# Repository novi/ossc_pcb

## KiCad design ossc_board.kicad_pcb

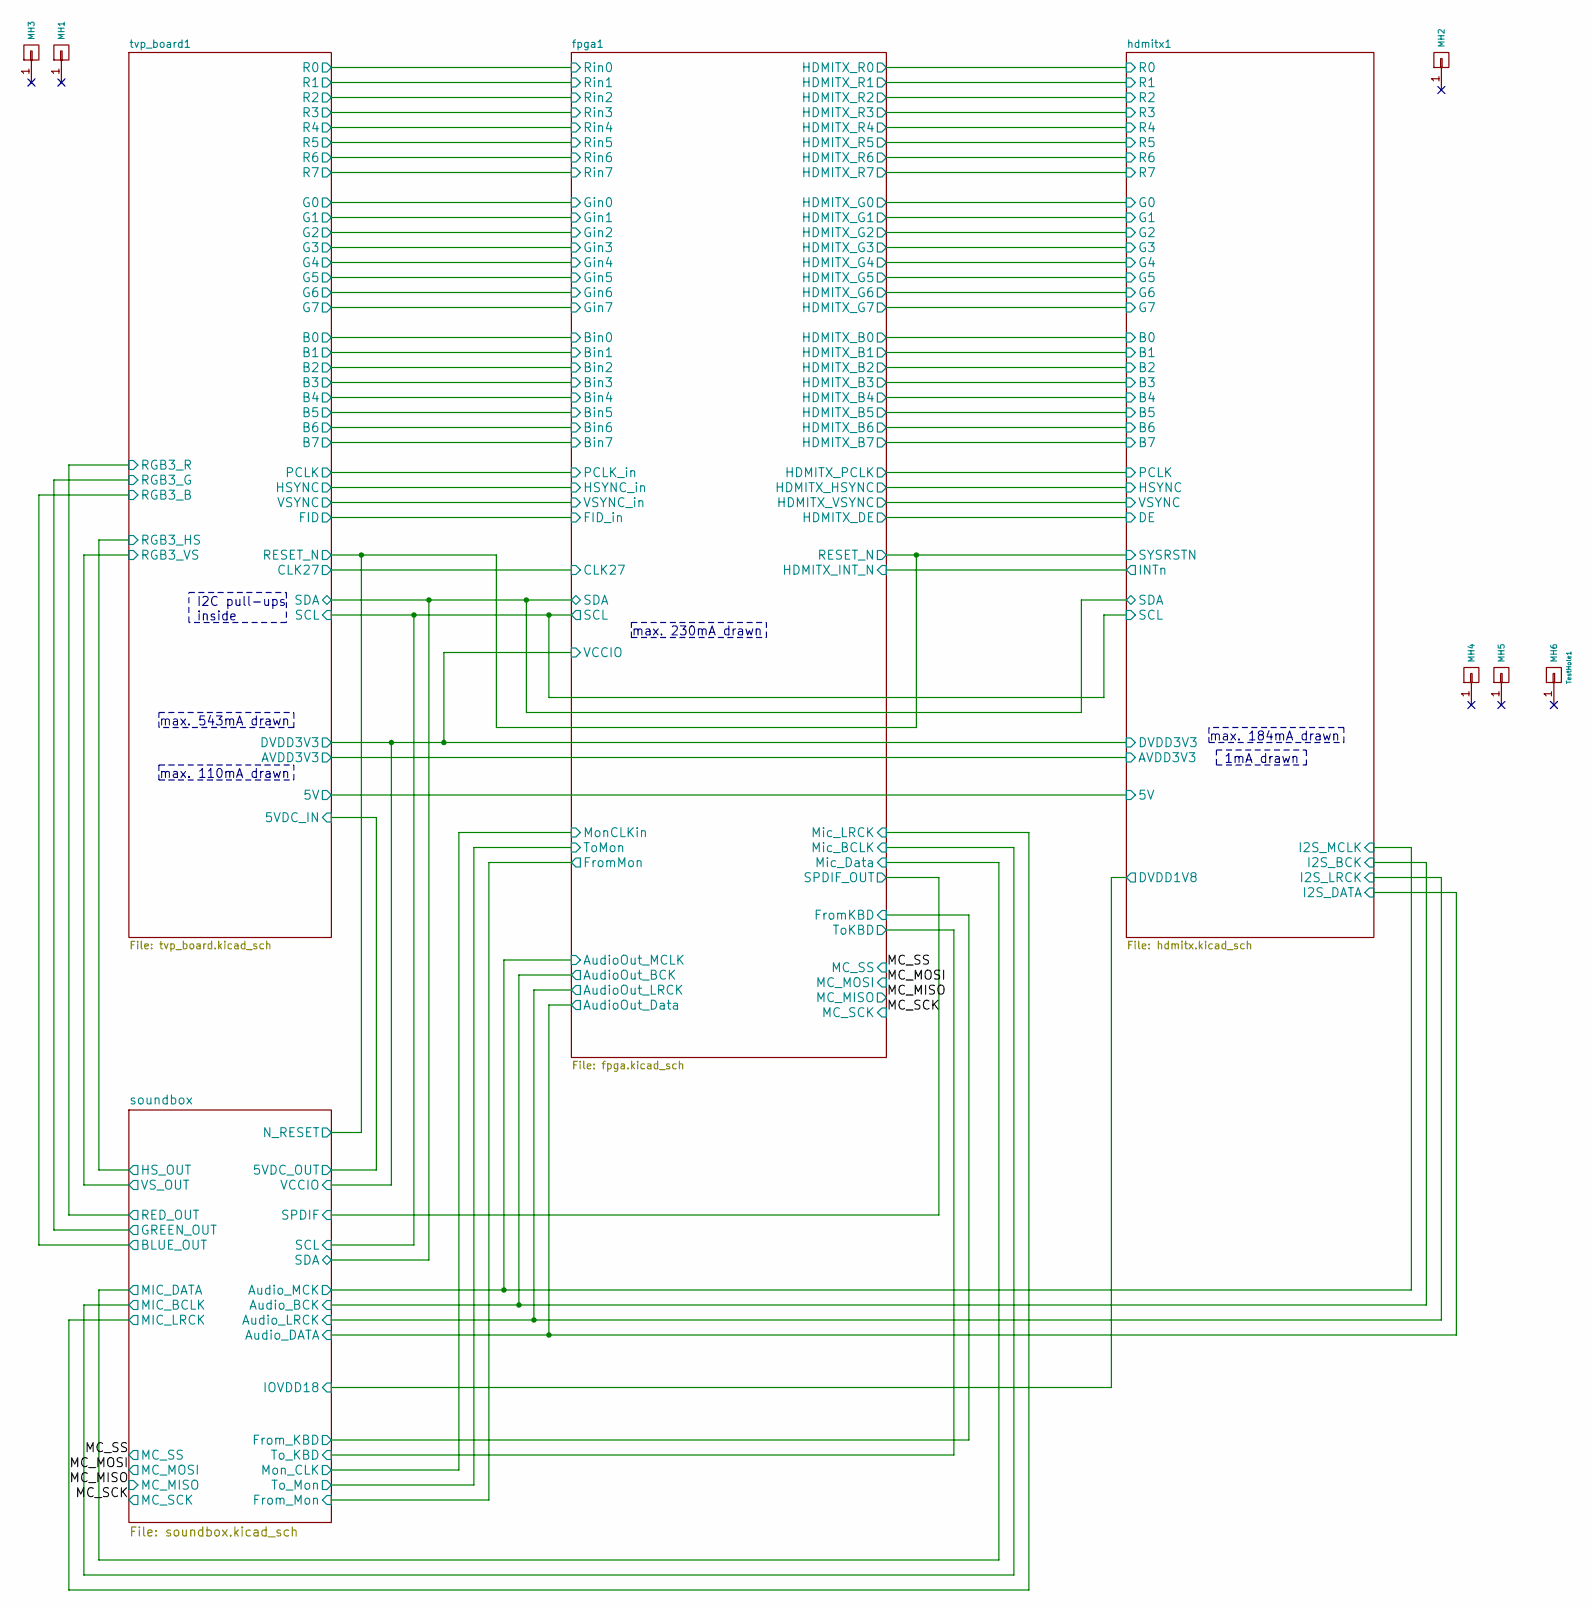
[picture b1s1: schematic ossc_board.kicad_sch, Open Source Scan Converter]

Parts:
MH1, MH2, MH3, MH4, MH5: CONN_1; MountingHole_2.7mm_M2.5
MH6: TestHole1; TestHole_1.0mm

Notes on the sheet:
1mA drawn
I2C pull-ups inside
max. 110mA drawn
max. 543mA drawn
max. 184mA drawn
max. 230mA drawn

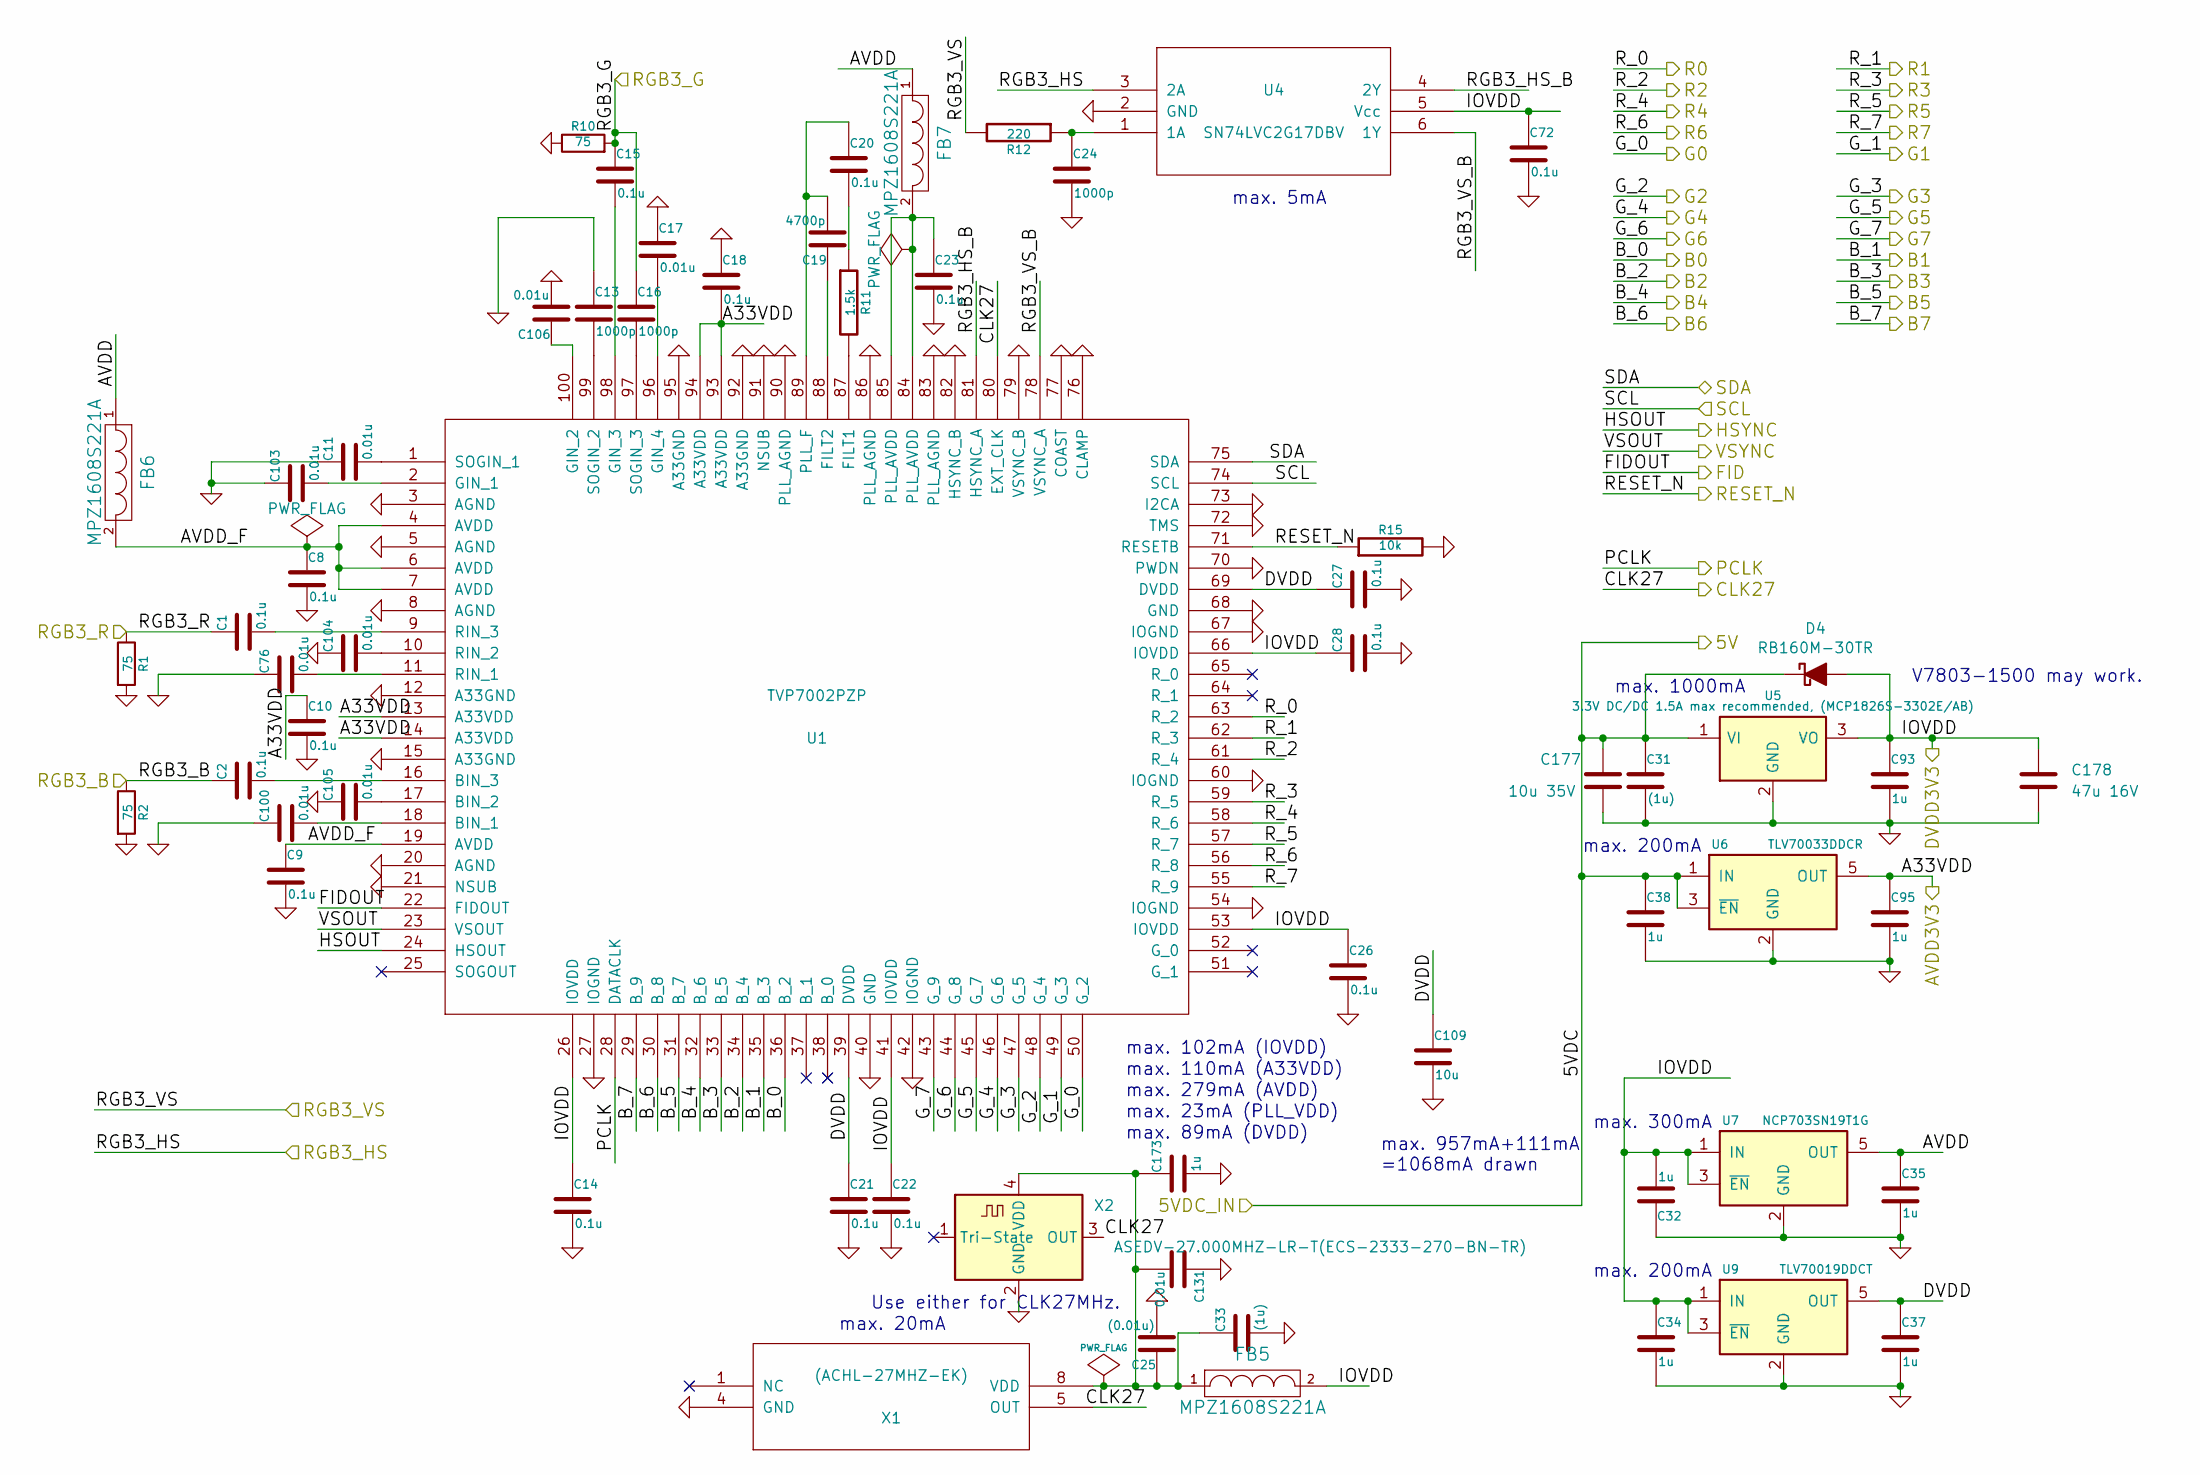
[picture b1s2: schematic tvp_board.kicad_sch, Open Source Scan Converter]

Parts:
C1, C2, C8, C9, C10, C14, C15, C18, C20, C21, C22, C23, C26, C27, C28, C72: 0.1u; C_0603_1608Metric_Pad1.05x0.95mm_HandSolder; Part ID GCJ188R71H104KA12D or GRM188R72A104MA35D
C11, C17, C76, C100, C103, C104, C105, C106, C131: 0.01u; C_0603_1608Metric_Pad1.05x0.95mm_HandSolder; Part ID GCM188R72A103KA37J
C13, C16, C24: 1000p; C_0603_1608Metric_Pad1.05x0.95mm_HandSolder
C19: 4700p; C_0603_1608Metric_Pad1.05x0.95mm_HandSolder
C25: (0.01u); C_0603_1608Metric_Pad1.05x0.95mm_HandSolder; Part ID GCM188R72A103KA37J
C31, C33: (1u); C_0603_1608Metric_Pad1.08x0.95mm_HandSolder; Part ID GRT188R61H105KE13D
C32, C34, C35, C37, C38, C93, C95, C173: 1u; C_0603_1608Metric_Pad1.05x0.95mm_HandSolder; Part ID GRT188R61H105KE13D
C109: 10u; C_0603_1608Metric_Pad1.05x0.95mm_HandSolder; Part ID ZRB18AR61E106ME01L
C177: 10u 35V; C_1210_3225Metric_Pad1.33x2.70mm_HandSolder; Part ID GRM32ER7YA106KA12
C178: 47u 16V; C_1210_3225Metric_Pad1.33x2.70mm_HandSolder; Part ID GRM32EC81C476KE15L
D4: RB160M-30TR; D_SOD-123_HandSoldering
FB5, FB6, FB7: MPZ1608S221A; L_0603_1608Metric_Pad1.05x0.95mm_HandSolder
R1, R2, R10: 75; R_0603_1608Metric_Pad1.05x0.95mm_HandSolder
R11: 1.5k; R_0603_1608Metric_Pad1.05x0.95mm_HandSolder
R12: 220; R_0603_1608Metric_Pad1.05x0.95mm_HandSolder
R15: 10k; R_0603_1608Metric_Pad1.05x0.95mm_HandSolder
U1: TVP7002PZP; TQFP-100_thermal
U4: SN74LVC2G17DBV; SOT-23-6_Handsoldering
U5: 3.3V DC/DC 1.5A max recommended, (MCP1826S-3302E/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; TO-220-3_Vertical; Part ID MCP1826S-3302E/AB
U6: TLV70033DDCR; SOT-23-5_HandSoldering
U7: NCP703SN19T1G; SOT-23-5_Handsoldering
U9: TLV70019DDCT; SOT-23-5_Handsoldering
X1: (ACHL-27MHZ-EK); ACHL-OSC
X2: ASEDV-27.000MHZ-LR-T(ECS-2333-270-BN-TR); Oscillator_SMD_SeikoEpson_SG8002CE-4Pin_3.2x2.5mm_HandSolde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

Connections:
/fpga1/RESET_N: R15.1, U1.71 (RESETB); also elsewhere on the board
/fpga1/SCL: U1.74 (SCL); also elsewhere on the board
/fpga1/SDA: U1.75 (SDA); also elsewhere on the board
/hdmitx1/5V: C31.1, C38.1, C177.1, D4.1 (K), U5.1 (VI), U6.1 (IN), U6.3 (~EN); also elsewhere on the board
/hdmitx1/AVCC3V3: C10.1, C18.2, C95.1, U1.13 (A33VDD), U1.14 (A33VDD), U1.93 (A33VDD), U1.94 (A33VDD), U6.5 (OUT); also elsewhere on the board
/tvp_board1/AVDD: C35.1, FB6.1, FB7.1, U7.5 (OUT)
/tvp_board1/AVDD_F: C8.1, C9.1, FB6.2, U1.4 (AVDD), U1.6 (AVDD), U1.7 (AVDD), U1.19 (AVDD)
/tvp_board1/B_0: U1.36 (B_2); also elsewhere on the board
/tvp_board1/B_1: U1.35 (B_3); also elsewhere on the board
/tvp_board1/B_2: U1.34 (B_4); also elsewhere on the board
/tvp_board1/B_3: U1.33 (B_5); also elsewhere on the board
/tvp_board1/B_4: U1.32 (B_6); also elsewhere on the board
/tvp_board1/B_5: U1.31 (B_7); also elsewhere on the board
/tvp_board1/B_6: U1.30 (B_8); also elsewhere on the board
/tvp_board1/B_7: U1.29 (B_9); also elsewhere on the board
/tvp_board1/CLK27: U1.80 (EXT_CLK), X1.5 (OUT), X2.3 (OUT); also elsewhere on the board
/tvp_board1/DVDD: C21.1, C27.1, C37.1, C109.1, U1.39 (DVDD), U1.69 (DVDD), U9.5 (OUT)
/tvp_board1/FIDOUT: U1.22 (FIDOUT); also elsewhere on the board
/tvp_board1/G_0: U1.50 (G_2); also elsewhere on the board
/tvp_board1/G_1: U1.49 (G_3); also elsewhere on the board
/tvp_board1/G_2: U1.48 (G_4); also elsewhere on the board
/tvp_board1/G_3: U1.47 (G_5); also elsewhere on the board
/tvp_board1/G_4: U1.46 (G_6); also elsewhere on the board
/tvp_board1/G_5: U1.45 (G_7); also elsewhere on the board
/tvp_board1/G_6: U1.44 (G_8); also elsewhere on the board
/tvp_board1/G_7: U1.43 (G_9); also elsewhere on the board
/tvp_board1/HSOUT: U1.24 (HSOUT); also elsewhere on the board
/tvp_board1/PCLK: U1.28 (DATACLK); also elsewhere on the board
/tvp_board1/RGB3_B: C2.1, R2.1; also elsewhere on the board
/tvp_board1/RGB3_G: C15.1, C16.1, R10.2; also elsewhere on the board
/tvp_board1/RGB3_HS: U4.3 (2A); also elsewhere on the board
/tvp_board1/RGB3_HS_B: U1.81 (HSYNC_A), U4.4 (2Y)
/tvp_board1/RGB3_R: C1.1, R1.1; also elsewhere on the board
/tvp_board1/RGB3_VS: R12.2; also elsewhere on the board
/tvp_board1/RGB3_VS_B: U1.78 (VSYNC_A), U4.6 (1Y)
/tvp_board1/R_0: U1.63 (R_2); also elsewhere on the board
/tvp_board1/R_1: U1.62 (R_3); also elsewhere on the board
/tvp_board1/R_2: U1.61 (R_4); also elsewhere on the board
/tvp_board1/R_3: U1.59 (R_5); also elsewhere on the board
/tvp_board1/R_4: U1.58 (R_6); also elsewhere on the board
/tvp_board1/R_5: U1.57 (R_7); also elsewhere on the board
/tvp_board1/R_6: U1.56 (R_8); also elsewhere on the board
/tvp_board1/R_7: U1.55 (R_9); also elsewhere on the board
/tvp_board1/VSOUT: U1.23 (VSOUT); also elsewhere on the board
GND: C8.2, C9.2, C10.2, C11.1, C13.1, C14.2, C17.1, C18.1, C21.2, C22.2, C23.2, C24.2, C25.2, C26.2, C27.2, C28.2, C31.2, C32.1, C33.2, C34.2, C35.2, C37.2, C38.2, C72.2, C76.1, C93.2, C95.2, C100.1, C103.1, C104.1, C105.1, C106.2, C109.2, C131.1, C173.2, C177.2, C178.2, R1.2, R2.2, R10.1, R15.2, U1.3 (AGND), U1.5 (AGND), U1.8 (AGND), U1.12 (A33GND), U1.15 (A33GND), U1.20 (AGND), U1.21 (NSUB), U1.27 (IOGND), U1.40 (GND), U1.42 (IOGND), U1.54 (IOGND), U1.60 (IOGND), U1.67 (IOGND), U1.68 (GND), U1.70 (PWDN), U1.72 (TMS), U1.73 (I2CA), U1.76 (CLAMP), U1.77 (COAST), U1.79 (VSYNC_B), U1.82 (HSYNC_B), U1.83 (PLL_AGND), U1.86 (PLL_AGND), U1.90 (PLL_AGND), U1.91 (NSUB), U1.92 (A33GND), U1.95 (A33GND), U4.2 (GND), U5.2 (GND), U6.2 (GND), U7.2 (GND), U9.2 (GND), X1.4 (GND), X2.2 (GND); also elsewhere on the board
unnamed: C20.2, R11.1
unnamed: C23.1, FB7.2, U1.84 (PLL_AVDD), U1.85 (PLL_AVDD)
unnamed: C100.2, U1.18 (BIN_1)
unnamed: C105.2, U1.17 (BIN_2)
unnamed: C2.2, U1.16 (BIN_3)
unnamed: R11.2, U1.87 (FILT1)
unnamed: C19.1, U1.88 (FILT2)
unnamed: C103.2, U1.2 (GIN_1)
unnamed: C106.1, U1.100 (GIN_2)
unnamed: C15.2, U1.98 (GIN_3)
unnamed: C17.2, U1.96 (GIN_4)
unnamed: C19.2, C20.1, U1.89 (PLL_F)
unnamed: C76.2, U1.11 (RIN_1)
unnamed: C104.2, U1.10 (RIN_2)
unnamed: C1.2, U1.9 (RIN_3)
unnamed: C11.2, U1.1 (SOGIN_1)
unnamed: C13.2, U1.99 (SOGIN_2)
unnamed: C16.2, U1.97 (SOGIN_3)
unnamed: C24.1, R12.1, U4.1 (1A)
unnamed: C25.1, C33.1, C131.2, C173.1, FB5.1, X1.8 (VDD), X2.4 (VDD)
VCC: C14.1, C22.1, C26.1, C28.1, C32.2, C34.1, C72.1, C93.1, C178.1, D4.2 (A), FB5.2, U1.26 (IOVDD), U1.41 (IOVDD), U1.53 (IOVDD), U1.66 (IOVDD), U4.5 (Vcc), U5.3 (VO), U7.1 (IN), U7.3 (~EN), U9.1 (IN), U9.3 (~EN); also elsewhere on the board

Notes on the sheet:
max. 1000mA
max. 110mA (A33VDD)
max. 279mA (AVDD)
max. 300mA
max. 23mA (PLL_VDD)
V7803-1500 may work.
max. 200mA
max. 957mA+111mA =1068mA drawn
max. 102mA (IOVDD)
Use either for CLK27MHz.
max. 5mA
max. 20mA
max. 89mA (DVDD)

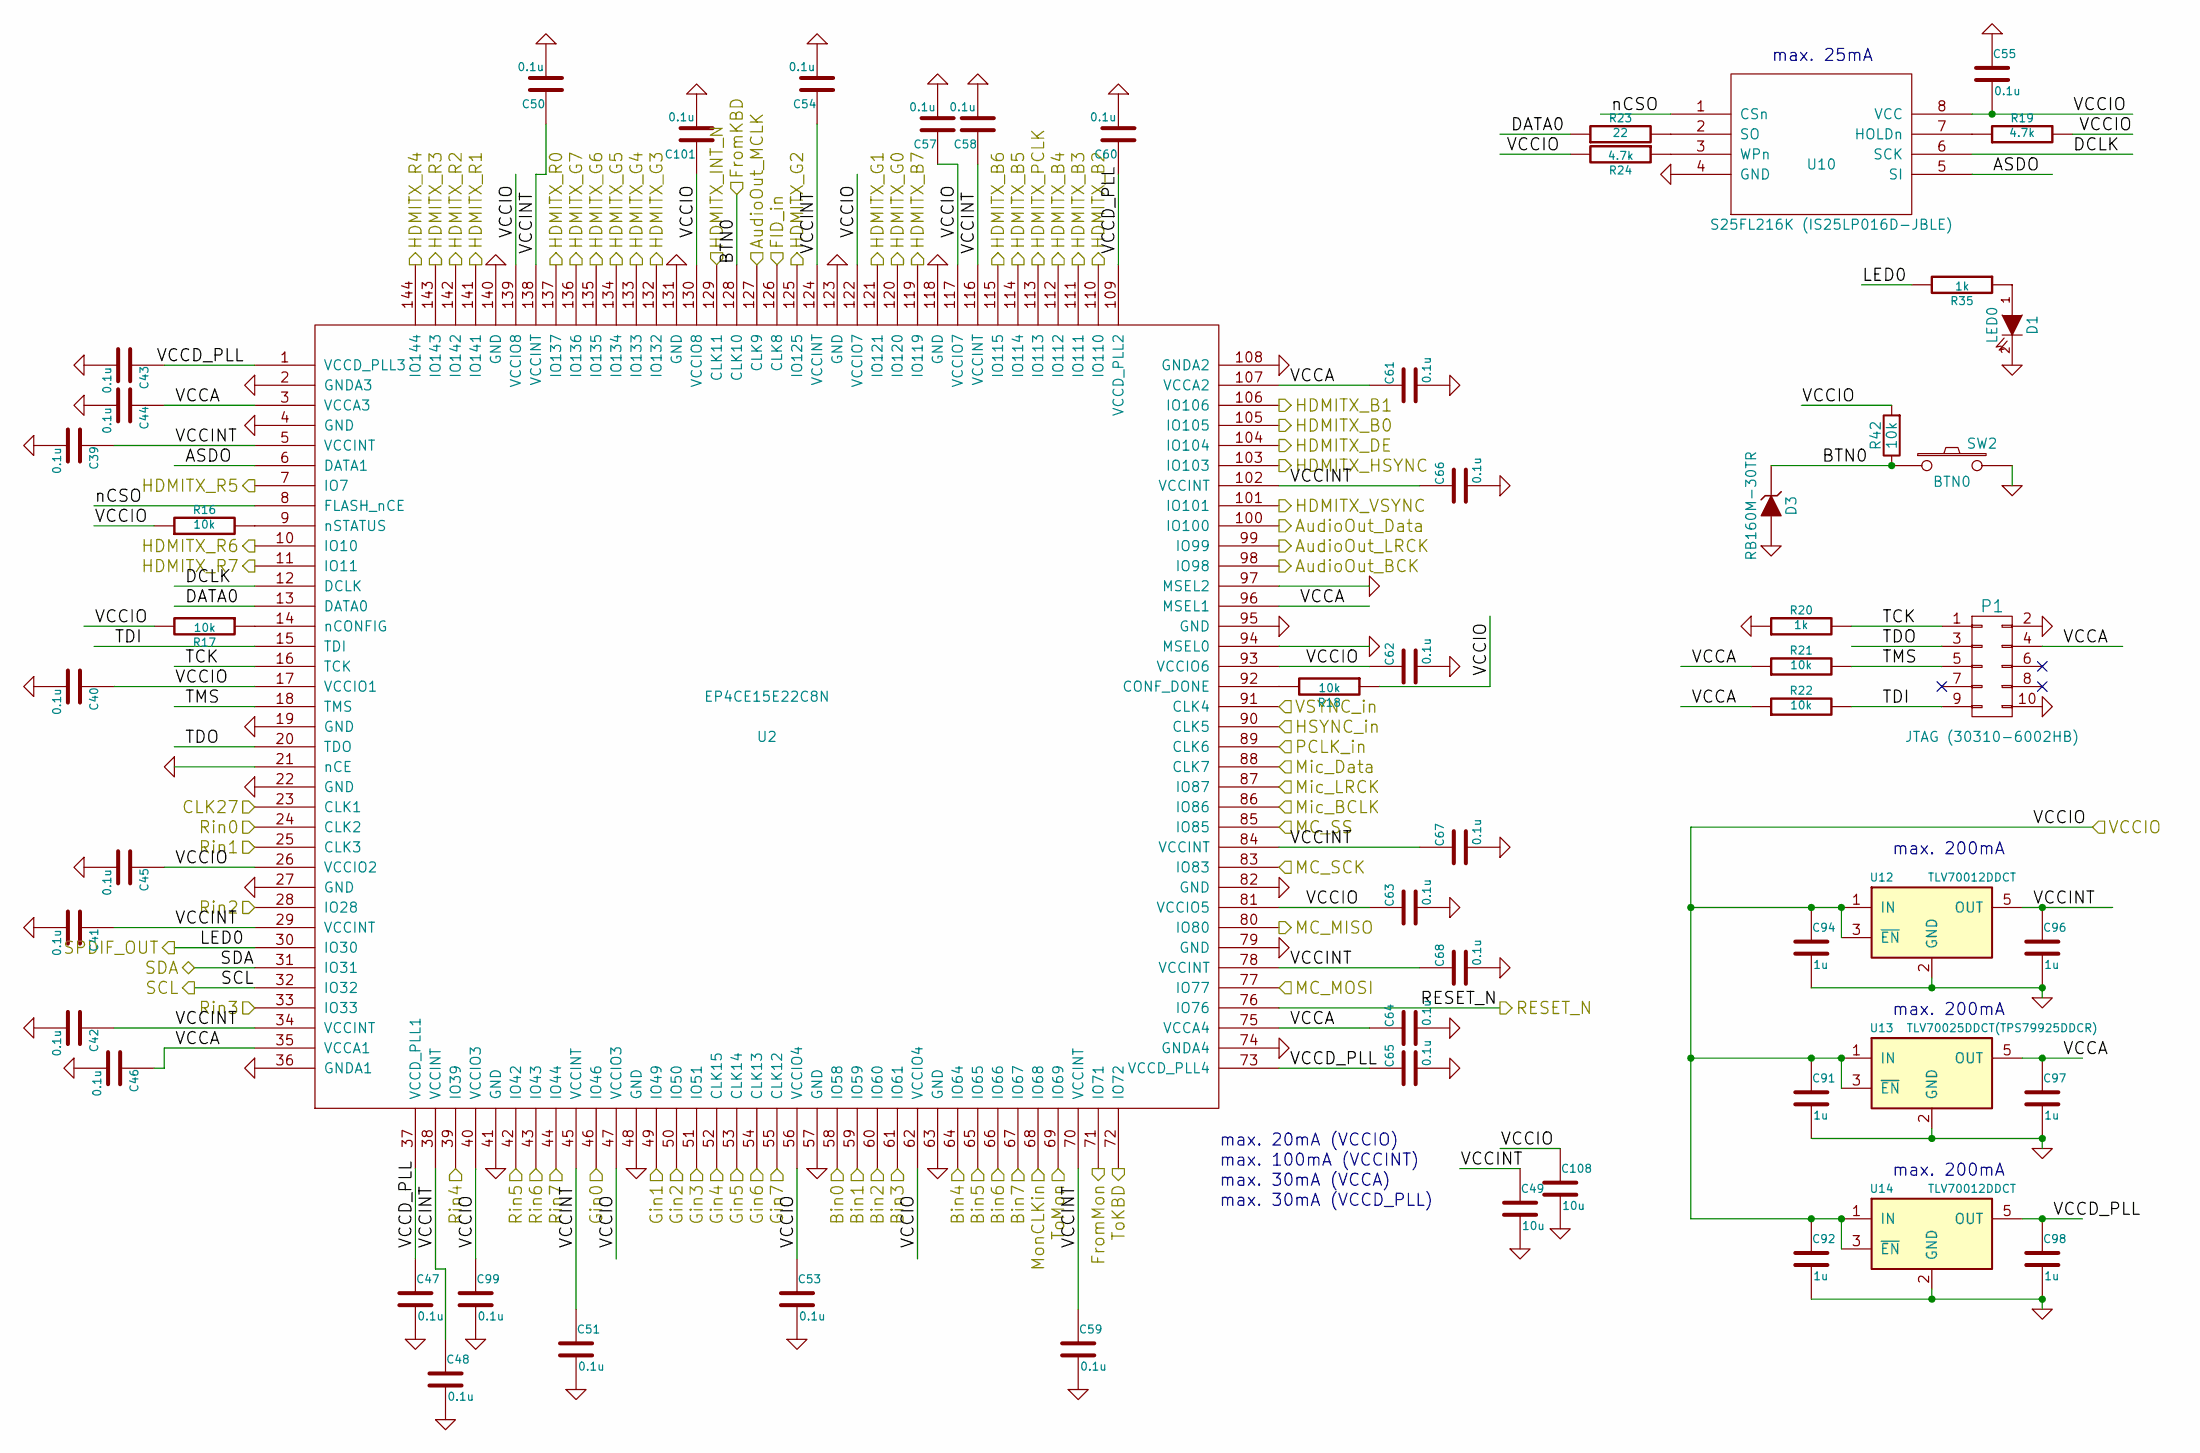
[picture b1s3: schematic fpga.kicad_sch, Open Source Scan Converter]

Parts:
C39, C40, C41, C42, C43, C44, C45, C46, C47, C48, C50, C51, C53, C54, C55, C57, C58, C59, C60, C61, C62, C63, C64, C65, C66, C67, C68, C99, C101: 0.1u; C_0603_1608Metric_Pad1.05x0.95mm_HandSolder; Part ID GCJ188R71H104KA12D or GRM188R72A104MA35D
C49, C108: 10u; C_0603_1608Metric_Pad1.05x0.95mm_HandSolder; Part ID ZRB18AR61E106ME01L
C91, C92, C94, C96, C97, C98: 1u; C_0603_1608Metric_Pad1.05x0.95mm_HandSolder; Part ID GRT188R61H105KE13D
D1: LED0; LED_D3.0mm_Horizontal_O1.27mm_Z6.0mm
D3: RB160M-30TR; D_SOD-123_HandSoldering
P1: JTAG (30310-6002HB); VASCH5x2
R16, R17, R18, R21, R22, R42: 10k; R_0603_1608Metric_Pad1.05x0.95mm_HandSolder
R19, R24: 4.7k; R_0603_1608Metric_Pad1.05x0.95mm_HandSolder
R20, R35: 1k; R_0603_1608Metric_Pad1.05x0.95mm_HandSolder
R23: 22; R_0603_1608Metric_Pad1.05x0.95mm_HandSolder
SW2: BTN0; SW_Tactile_SKHH_Angled; Part ID (1-1825027-1 / 2-1825027-0)
U2: EP4CE15E22C8N; TQFP-144_thermal
U10: S25FL216K (IS25LP016D-JBLE); SOIC-8_3.9x4.9mm_Pitch1.27mm_Handsoldering
U12, U14: TLV70012DDCT; SOT-23-5_Handsoldering
U13: TLV70025DDCT(TPS79925DDCR); SOT-23-5_Handsoldering

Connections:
/MC_MISO: U2.80 (IO80); also elsewhere on the board
/MC_MOSI: U2.77 (IO77); also elsewhere on the board
/MC_SCK: U2.83 (IO83); also elsewhere on the board
/MC_SS: U2.85 (IO85); also elsewhere on the board
/fpga1/ASDO: U2.6 (DATA1), U10.5 (SI)
/fpga1/BTN0: D3.1 (K), R42.1, SW2.1, U2.128 (CLK10); also elsewhere on the board
/fpga1/DATA0: R23.1, U2.13 (DATA0)
/fpga1/DCLK: U2.12 (DCLK), U10.6 (SCK)
/fpga1/FromMon: U2.71 (IO71); also elsewhere on the board
/fpga1/HDMITX_B0: U2.105 (IO105); also elsewhere on the board
/fpga1/HDMITX_B1: U2.106 (IO106); also elsewhere on the board
/fpga1/HDMITX_B2: U2.110 (IO110); also elsewhere on the board
/fpga1/HDMITX_B3: U2.111 (IO111); also elsewhere on the board
/fpga1/HDMITX_B4: U2.112 (IO112); also elsewhere on the board
/fpga1/HDMITX_B5: U2.114 (IO114); also elsewhere on the board
/fpga1/HDMITX_B6: U2.115 (IO115); also elsewhere on the board
/fpga1/HDMITX_B7: U2.119 (IO119); also elsewhere on the board
/fpga1/HDMITX_DE: U2.104 (IO104); also elsewhere on the board
/fpga1/HDMITX_G0: U2.120 (IO120); also elsewhere on the board
/fpga1/HDMITX_G1: U2.121 (IO121); also elsewhere on the board
/fpga1/HDMITX_G2: U2.125 (IO125); also elsewhere on the board
/fpga1/HDMITX_G3: U2.132 (IO132); also elsewhere on the board
/fpga1/HDMITX_G4: U2.133 (IO133); also elsewhere on the board
/fpga1/HDMITX_G5: U2.134 (IO134); also elsewhere on the board
/fpga1/HDMITX_G6: U2.135 (IO135); also elsewhere on the board
/fpga1/HDMITX_G7: U2.136 (IO136); also elsewhere on the board
/fpga1/HDMITX_HSYNC: U2.103 (IO103); also elsewhere on the board
/fpga1/HDMITX_INT_N: U2.129 (CLK11); also elsewhere on the board
/fpga1/HDMITX_PCLK: U2.113 (IO113); also elsewhere on the board
/fpga1/HDMITX_R0: U2.137 (IO137); also elsewhere on the board
/fpga1/HDMITX_R1: U2.141 (IO141); also elsewhere on the board
/fpga1/HDMITX_R2: U2.142 (IO142); also elsewhere on the board
/fpga1/HDMITX_R3: U2.143 (IO143); also elsewhere on the board
/fpga1/HDMITX_R4: U2.144 (IO144); also elsewhere on the board
/fpga1/HDMITX_R5: U2.7 (IO7); also elsewhere on the board
/fpga1/HDMITX_R6: U2.10 (IO10); also elsewhere on the board
/fpga1/HDMITX_R7: U2.11 (IO11); also elsewhere on the board
/fpga1/HDMITX_VSYNC: U2.101 (IO101); also elsewhere on the board
/fpga1/LED0: R35.2, U2.30 (IO30); also elsewhere on the board
/fpga1/Mic_BCLK: U2.86 (IO86); also elsewhere on the board
/fpga1/Mic_Data: U2.88 (CLK7); also elsewhere on the board
/fpga1/Mic_LRCK: U2.87 (IO87); also elsewhere on the board
/fpga1/MonCLKin: U2.68 (IO68); also elsewhere on the board
/fpga1/RESET_N: U2.76 (IO76); also elsewhere on the board
/fpga1/SCL: U2.32 (IO32); also elsewhere on the board
/fpga1/SDA: U2.31 (IO31); also elsewhere on the board
/fpga1/TCK: P1.1, R20.2, U2.16 (TCK)
/fpga1/TDI: P1.9, R22.2, U2.15 (TDI)
/fpga1/TDO: P1.3, U2.20 (TDO)
/fpga1/TMS: P1.5, R21.2, U2.18 (TMS)
/fpga1/ToKBD: U2.72 (IO72); also elsewhere on the board
/fpga1/ToMon: U2.69 (IO69); also elsewhere on the board
/fpga1/VCCA: C44.1, C46.1, C61.1, C64.1, C97.1, P1.4, R21.1, R22.1, U2.3 (VCCA3), U2.35 (VCCA1), U2.75 (VCCA4), U2.96 (MSEL1), U2.107 (VCCA2), U13.5 (OUT)
/fpga1/VCCD_PLL: C43.1, C47.1, C60.1, C65.1, C98.1, U2.1 (VCCD_PLL3), U2.37 (VCCD_PLL1), U2.73 (VCCD_PLL4), U2.109 (VCCD_PLL2), U14.5 (OUT)
/fpga1/VCCINT: C39.1, C41.1, C42.1, C48.1, C49.1, C50.1, C51.1, C54.1, C58.1, C59.1, C66.1, C67.1, C68.1, C96.1, U2.5 (VCCINT), U2.29 (VCCINT), U2.34 (VCCINT), U2.38 (VCCINT), U2.45 (VCCINT), U2.70 (VCCINT), U2.78 (VCCINT), U2.84 (VCCINT), U2.102 (VCCINT), U2.116 (VCCINT), U2.124 (VCCINT), U2.138 (VCCINT), U12.5 (OUT)
/fpga1/nCSO: U2.8 (FLASH_nCE), U10.1 (CSn)
/hdmitx1/I2S_BCK: U2.98 (IO98); also elsewhere on the board
/hdmitx1/I2S_DATA: U2.100 (IO100); also elsewhere on the board
/hdmitx1/I2S_LRCK: U2.99 (IO99); also elsewhere on the board
/soundbox/MCLK: U2.127 (CLK9); also elsewhere on the board
/tvp_board1/B_0: U2.58 (IO58); also elsewhere on the board
/tvp_board1/B_1: U2.59 (IO59); also elsewhere on the board
/tvp_board1/B_2: U2.60 (IO60); also elsewhere on the board
/tvp_board1/B_3: U2.61 (IO61); also elsewhere on the board
/tvp_board1/B_4: U2.64 (IO64); also elsewhere on the board
/tvp_board1/B_5: U2.65 (IO65); also elsewhere on the board
/tvp_board1/B_6: U2.66 (IO66); also elsewhere on the board
/tvp_board1/B_7: U2.67 (IO67); also elsewhere on the board
/tvp_board1/CLK27: U2.23 (CLK1); also elsewhere on the board
/tvp_board1/FIDOUT: U2.126 (CLK8); also elsewhere on the board
/tvp_board1/G_0: U2.46 (IO46); also elsewhere on the board
/tvp_board1/G_1: U2.49 (IO49); also elsewhere on the board
/tvp_board1/G_2: U2.50 (IO50); also elsewhere on the board
/tvp_board1/G_3: U2.51 (IO51); also elsewhere on the board
/tvp_board1/G_4: U2.52 (CLK15); also elsewhere on the board
/tvp_board1/G_5: U2.53 (CLK14); also elsewhere on the board
/tvp_board1/G_6: U2.54 (CLK13); also elsewhere on the board
/tvp_board1/G_7: U2.55 (CLK12); also elsewhere on the board
/tvp_board1/HSOUT: U2.90 (CLK5); also elsewhere on the board
/tvp_board1/PCLK: U2.89 (CLK6); also elsewhere on the board
/tvp_board1/R_0: U2.24 (CLK2); also elsewhere on the board
/tvp_board1/R_1: U2.25 (CLK3); also elsewhere on the board
/tvp_board1/R_2: U2.28 (IO28); also elsewhere on the board
/tvp_board1/R_3: U2.33 (IO33); also elsewhere on the board
/tvp_board1/R_4: U2.39 (IO39); also elsewhere on the board
/tvp_board1/R_5: U2.42 (IO42); also elsewhere on the board
/tvp_board1/R_6: U2.43 (IO43); also elsewhere on the board
/tvp_board1/R_7: U2.44 (IO44); also elsewhere on the board
/tvp_board1/VSOUT: U2.91 (CLK4); also elsewhere on the board
GND: C39.2, C40.2, C41.2, C42.2, C43.2, C44.2, C45.2, C46.2, C47.2, C48.2, C49.2, C50.2, C51.2, C53.2, C54.2, C55.1, C57.2, C58.2, C59.2, C60.2, C61.2, C62.2, C63.2, C64.2, C65.2, C66.2, C67.2, C68.2, C91.2, C92.2, C94.2, C96.2, C97.2, C98.2, C99.2, C101.2, C108.2, D1.2 (K), D3.2 (A), P1.2, P1.10, R20.1, SW2.2, U2.2 (GNDA3), U2.4 (GND), U2.19 (GND), U2.21 (nCE), U2.22 (GND), U2.27 (GND), U2.36 (GNDA1), U2.41 (GND), U2.48 (GND), U2.57 (GND), U2.63 (GND), U2.74 (GNDA4), U2.79 (GND), U2.82 (GND), U2.94 (MSEL0), U2.95 (GND), U2.97 (MSEL2), U2.108 (GNDA2), U2.118 (GND), U2.123 (GND), U2.131 (GND), U2.140 (GND), U10.4 (GND), U12.2 (GND), U13.2 (GND), U14.2 (GND); also elsewhere on the board
unnamed: D1.1 (A), R35.1
unnamed: R18.2, U2.92 (CONF_DONE)
unnamed: R17.1, U2.14 (nCONFIG)
unnamed: R16.2, U2.9 (nSTATUS)
unnamed: R19.1, U10.7 (HOLDn)
unnamed: R23.2, U10.2 (SO)
unnamed: R24.1, U10.3 (WPn)
VCC: C40.1, C45.1, C53.1, C55.2, C57.1, C62.1, C63.1, C91.1, C92.1, C94.1, C99.1, C101.1, C108.1, R16.1, R17.2, R18.1, R19.2, R24.2, R42.2, U2.17 (VCCIO1), U2.26 (VCCIO2), U2.40 (VCCIO3), U2.47 (VCCIO3), U2.56 (VCCIO4), U2.62 (VCCIO4), U2.81 (VCCIO5), U2.93 (VCCIO6), U2.117 (VCCIO7), U2.122 (VCCIO7), U2.130 (VCCIO8), U2.139 (VCCIO8), U10.8 (VCC), U12.1 (IN), U12.3 (~EN), U13.1 (IN), U13.3 (~EN), U14.1 (IN), U14.3 (~EN); also elsewhere on the board

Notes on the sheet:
max. 30mA (VCCA)
max. 20mA (VCCIO)
max. 200mA
max. 25mA
max. 100mA (VCCINT)
max. 30mA (VCCD_PLL)
